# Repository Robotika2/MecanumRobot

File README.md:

# MecanumRobot
Mecanum robot, literally

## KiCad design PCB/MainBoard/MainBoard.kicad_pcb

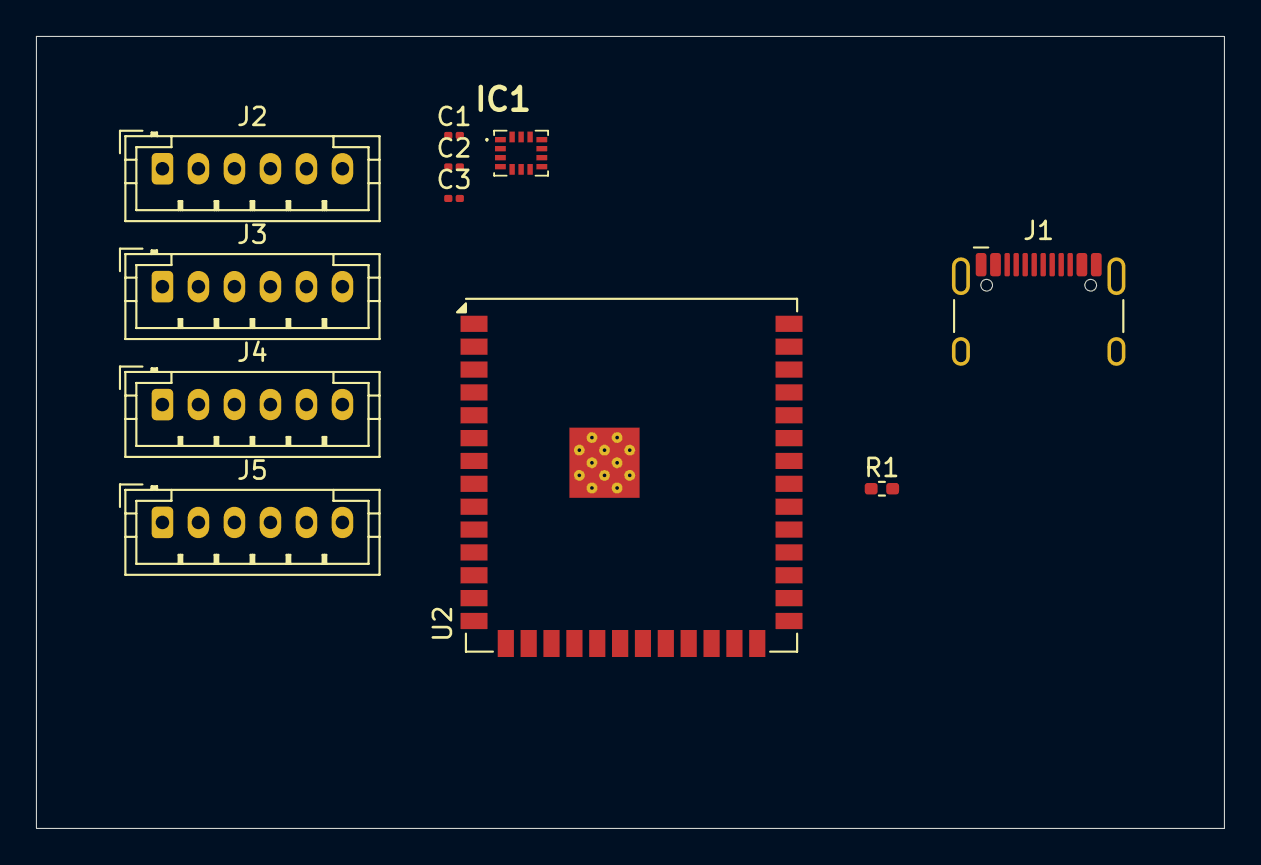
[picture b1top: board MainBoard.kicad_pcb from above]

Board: 2 copper layers, 66.0 x 44.0 mm, 11 parts (0 on the bottom side), 6 nets, no tracks yet.

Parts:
C1: 10nF; C_0201_0603Metric
C2, C3: 0.1uF; C_0201_0603Metric
IC1: ICM-42670-P; ICM42670P
J1: USB_C_Receptacle_USB2.0_14P; USB_C_Receptacle_HCTL_HC-TYPE-C-16P-01A
J2, J3, J4, J5: Conn_01x06_Pin; JST_PH_B6B-PH-K_1x06_P2.00mm_Vertical
R1: 1M; R_0402_1005Metric_Pad0.72x0.64mm_HandSolder
U2: ESP32-S3-WROOM-1; ESP32-S3-WROOM-1U

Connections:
+3.3V: C1.1, C2.1, C3.1, IC1.5 (VDDIO), IC1.8 (VDD), IC1.12 (AP_CS), U2.2 (3V3), U2.3 (EN)
/MCU/USB_D+: J1.A6 (D+), J1.B6 (D+), U2.14 (USB_D+)
/MCU/USB_D-: J1.A7 (D-), J1.B7 (D-), U2.13 (USB_D-)
GND: C1.2, C2.2, C3.2, IC1.6 (GND), IC1.7 (FSYNC), J1.A1 (GND), J1.A12 (GND), J1.B1 (GND), J1.B12 (GND), R1.2, U2.1 (GND), U2.40 (GND), U2.41 (GND)
unnamed: J1.S1 (SHIELD), R1.1
unnamed: J1.A4 (VBUS), J1.A9 (VBUS), J1.B4 (VBUS), J1.B9 (VBUS)

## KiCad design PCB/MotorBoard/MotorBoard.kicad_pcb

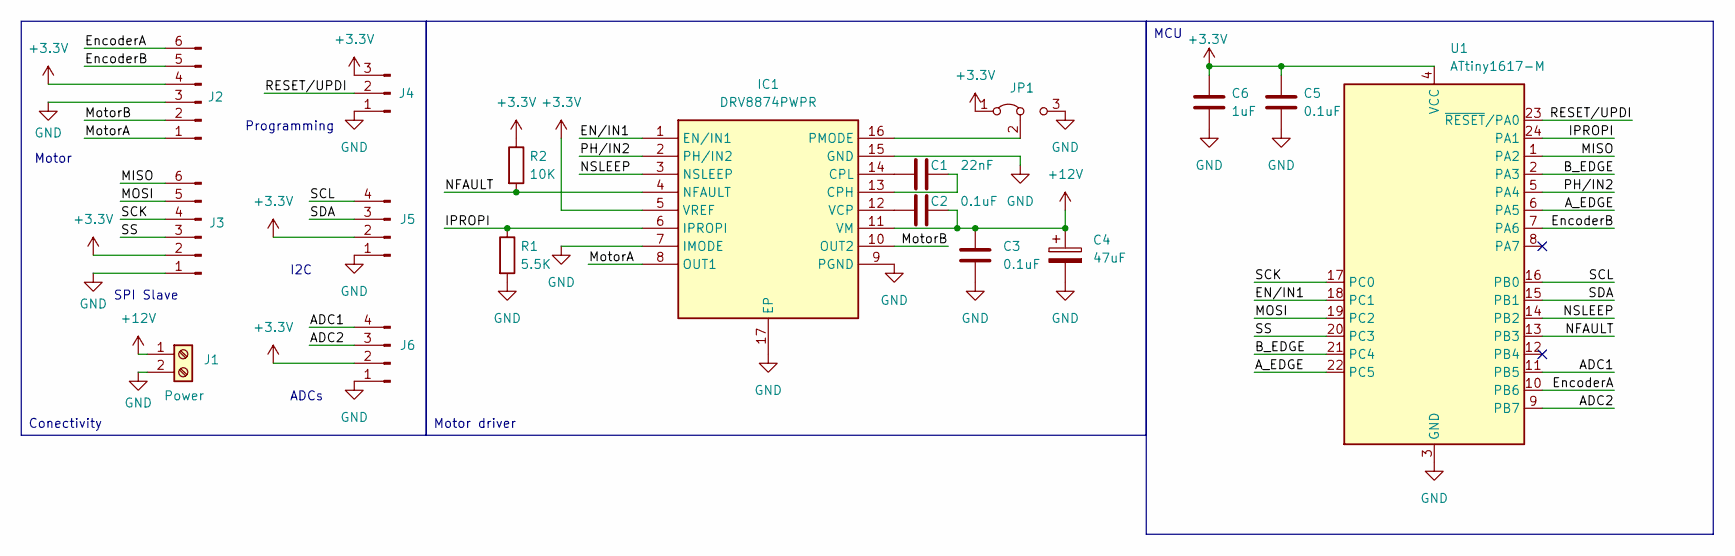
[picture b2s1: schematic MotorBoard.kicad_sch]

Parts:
C1: 22nF; C_0603_1608Metric
C2, C3, C5: 0.1uF; C_0603_1608Metric
C4: 47uF; CP_EIA-7343-15_Kemet-W
C6: 1uF; C_0603_1608Metric
IC1: DRV8874PWPR; HTSSOP-16-1EP_4.4x5mm_P0.65mm_EP3.4x5mm_Mask2.46x2.31mm_The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; Mouser Part Number 595-DRV8874PWPR
J1: Power; JST_VH_B2P-VH-FB-B_1x02_P3.96mm_Vertical
J2: Conn_01x06_Pin; PinHeader_1x06_P2.54mm_Vertical
J3: Conn_01x06_Pin; JST_PH_B6B-PH-K_1x06_P2.00mm_Vertical
J4: Conn_01x03_Pin; PinHeader_1x03_P2.00mm_Vertical
J5, J6: Conn_01x04_Pin; PinHeader_1x04_P2.00mm_Vertical
JP1: Jumper_3_Bridged12; SolderJumper-3_P1.3mm_Bridged2Bar12_RoundedPad1.0x1.5mm_Num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
R1: 5.5K; R_0603_1608Metric
R2: 10K; R_0603_1608Metric
U1: ATtiny1617-M; QFN-24-1EP_4x4mm_P0.5mm_EP2.6x2.6mm

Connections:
+3.3V: C5.1, C6.1, IC1.5 (VREF), J2.4, J3.2, J4.3, J5.2, J6.2, JP1.1 (A), R2.1, U1.4 (VCC)
+12V: C2.2, C3.1, C4.1, IC1.11 (VM), J1.1
/ADC1: J6.4, U1.11 (PB5)
/ADC2: J6.3, U1.9 (PB7)
/A_EDGE: U1.6 (PA5), U1.22 (PC5)
/B_EDGE: U1.2 (PA3), U1.21 (PC4)
/EN/IN1: IC1.1 (EN/IN1), U1.18 (PC1)
/EncoderA: J2.6, U1.10 (PB6)
/EncoderB: J2.5, U1.7 (PA6)
/IPROPI: IC1.6 (IPROPI), R1.1, U1.24 (PA1)
/MISO: J3.6, U1.1 (PA2)
/MOSI: J3.5, U1.19 (PC2)
/MotorA: IC1.8 (OUT1), J2.1
/MotorB: IC1.10 (OUT2), J2.2
/NFAULT: IC1.4 (NFAULT), R2.2, U1.13 (PB3)
/NSLEEP: IC1.3 (NSLEEP), U1.14 (PB2)
/PH/IN2: IC1.2 (PH/IN2), U1.5 (PA4)
/RESET/UPDI: J4.2, U1.23 (~RESET/PA0)
/SCK: J3.4, U1.17 (PC0)
/SCL: J5.4, U1.16 (PB0)
/SDA: J5.3, U1.15 (PB1)
/SS: J3.3, U1.20 (PC3)
GND: C3.2, C4.2, C5.2, C6.2, IC1.7 (IMODE), IC1.9 (PGND), IC1.15 (GND), IC1.17 (EP), J1.2, J2.3, J3.1, J4.1, J5.1, J6.1, JP1.3 (B), R1.2, U1.3 (GND), U1.25 (GND)
unnamed: C1.2, IC1.13 (CPH)
unnamed: C1.1, IC1.14 (CPL)
unnamed: IC1.16 (PMODE), JP1.2 (C)
unnamed: C2.1, IC1.12 (VCP)

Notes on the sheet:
I2C
Motor
Programming
SPI Slave
ADCs
Conectivity
Motor driver
MCU

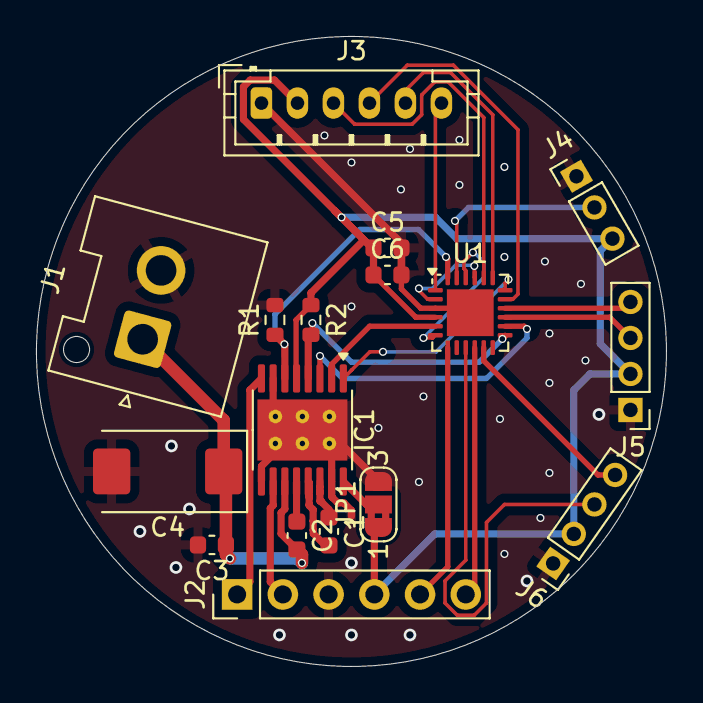
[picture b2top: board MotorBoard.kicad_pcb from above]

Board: 2 copper layers, 35.0 x 35.0 mm, 17 parts (0 on the bottom side), 27 nets.

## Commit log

2025-01-23 pcb start
2025-01-23 ehmm smal fix
2025-01-23 moved to 3D folder
2025-01-23 small workdir fixes
2025-01-23 edit LICENSE
2025-01-23 added batteryboard + more workdir cleanup
2025-01-23 Added schematics for motor driver
2025-01-30 Added IMU (just copied it tho...)
2025-02-06 Added MCU and started work on it
2025-02-20 MCU scheme done
2025-02-23 Changed to new processor and done schematic for it
2025-03-07 Changed mcu again
2025-03-09 Choosed some packages for components
2025-03-10 found all footprints for components
2025-04-03 Repaired IMU and ESP symbols and footprints
2025-04-03 Some minor changes
2025-04-03 Added some 3D models to components
2025-05-22 Added Buck converter
